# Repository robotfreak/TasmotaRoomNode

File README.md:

# TasmotaRoomNode
A home automation ESP room node using Tasmota

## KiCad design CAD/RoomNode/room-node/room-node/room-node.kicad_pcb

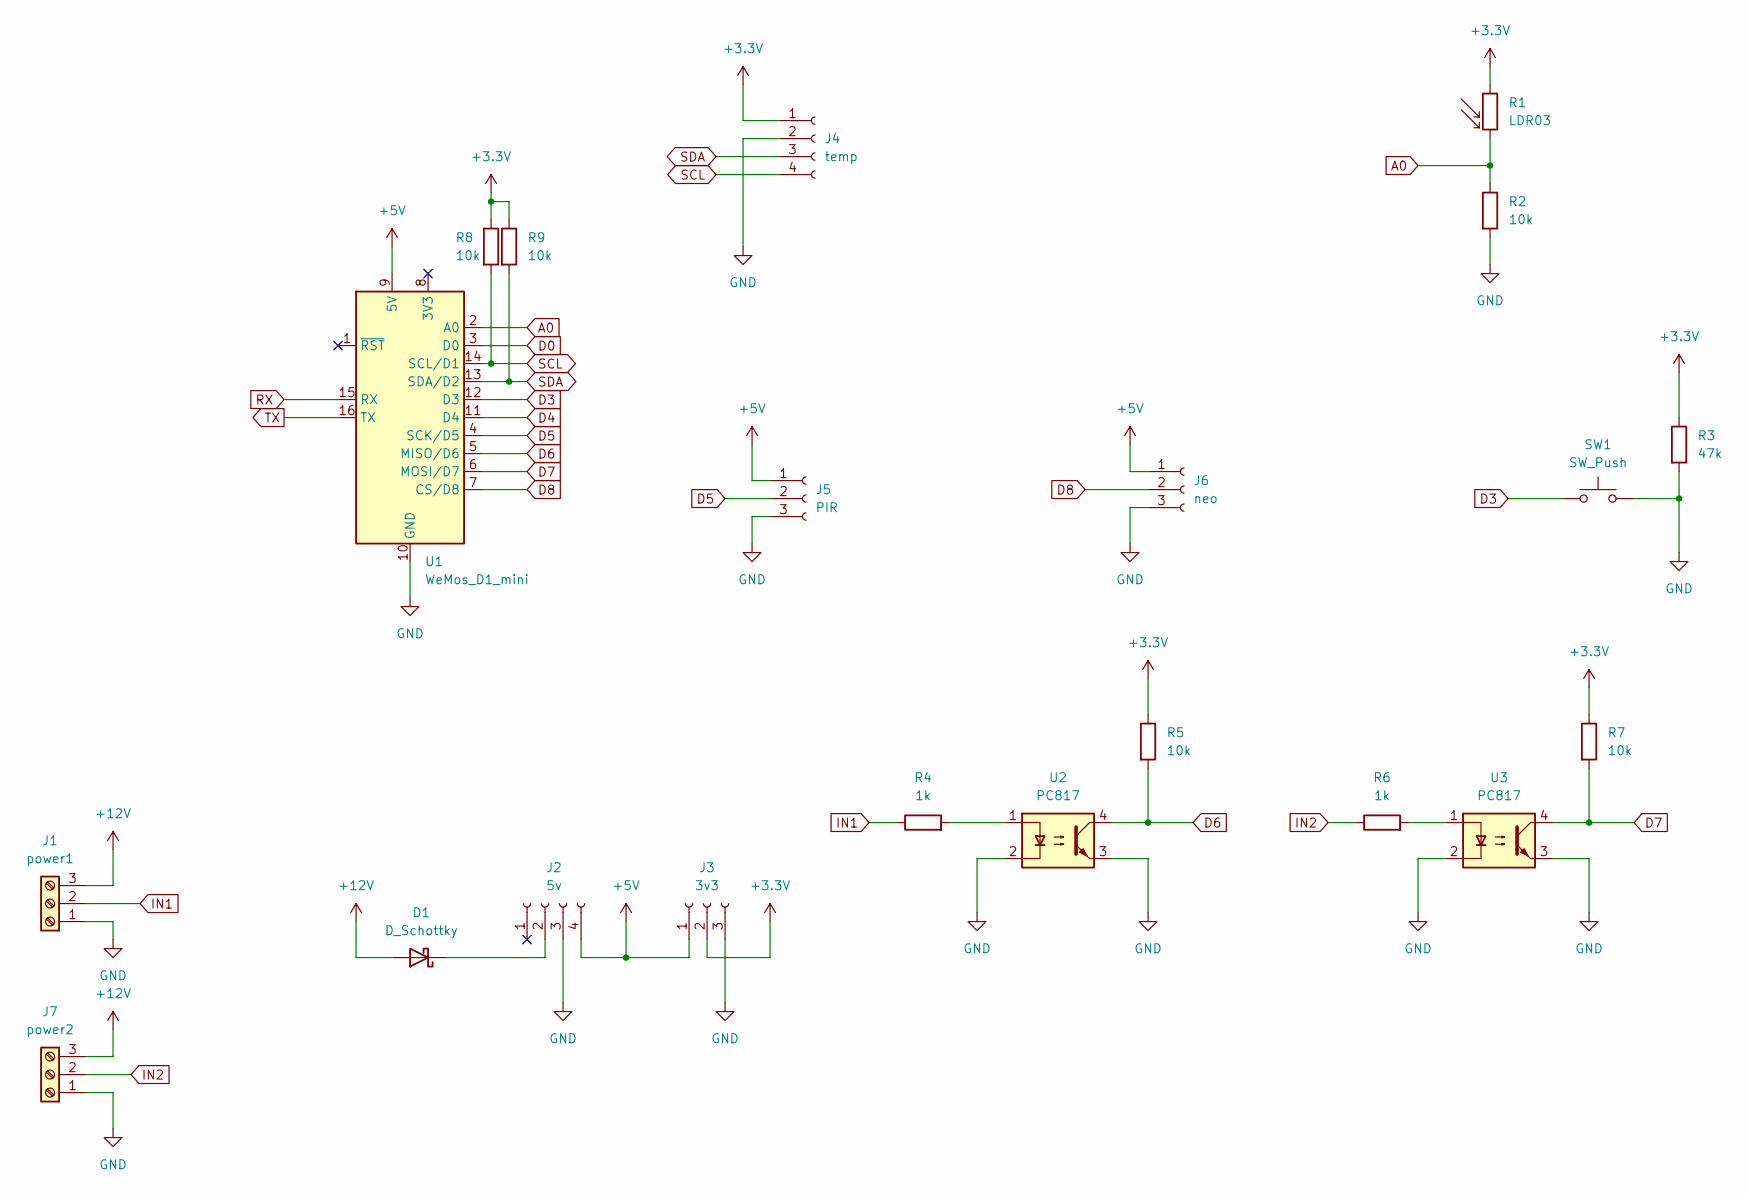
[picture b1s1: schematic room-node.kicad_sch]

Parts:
D1: D_Schottky; D_SMA
J1: power1; TerminalBlock_bornier-3_P5.08mm
J2: 5v; PinSocket_1x04_P2.54mm_Vertical
J3: 3v3; PinSocket_1x03_P2.54mm_Vertical
J4: temp; PinSocket_1x04_P2.54mm_Vertical
J5: PIR; PinSocket_1x03_P2.54mm_Vertical
J6: neo; PinSocket_1x03_P2.54mm_Vertical
J7: power2; TerminalBlock_bornier-3_P5.08mm
R1: LDR03; R_LDR_4.9x4.2mm_P2.54mm_Vertical
R2, R5, R7, R8, R9: 10k; R_0805_2012Metric
R3: 47k; R_0805_2012Metric
R4, R6: 1k; R_0805_2012Metric
SW1: SW_Push; SW_PUSH_6mm
U1: WeMos_D1_mini; WEMOS_D1_mini_light
U2, U3: PC817; DIP-4_W7.62mm

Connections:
+3.3V: J3.2, J4.1, R1.1, R3.1, R5.1, R7.1, R8.1, R9.1
+5V: J2.4, J3.1, J5.1, J6.1, U1.9 (5V)
+12V: D1.2 (A), J1.3, J7.3
A0: R1.2, R2.1, U1.2 (A0)
D0: U1.3 (D0)
D3: SW1.1, U1.12 (D3)
D4: U1.11 (D4)
D5: J5.2, U1.4 (SCK/D5)
D6: R5.2, U1.5 (MISO/D6), U2.4
D7: R7.2, U1.6 (MOSI/D7), U3.4
D8: J6.2, U1.7 (CS/D8)
GND: J1.1, J2.3, J3.3, J4.2, J5.3, J6.3, J7.1, R2.2, R3.2, SW1.2, U1.10 (GND), U2.2, U2.3, U3.2, U3.3
IN1: J1.2, R4.1
IN2: J7.2, R6.1
unnamed: D1.1 (K), J2.2
unnamed: R4.2, U2.1
unnamed: R6.2, U3.1
RX: U1.15 (RX)
SCL: J4.4, R8.2, U1.14 (SCL/D1)
SDA: J4.3, R9.2, U1.13 (SDA/D2)
TX: U1.16 (TX)

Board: 2 copper layers, 21 parts (16 on the bottom side), 17 nets, no tracks yet.

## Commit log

2023-04-17 added room-node schematic
